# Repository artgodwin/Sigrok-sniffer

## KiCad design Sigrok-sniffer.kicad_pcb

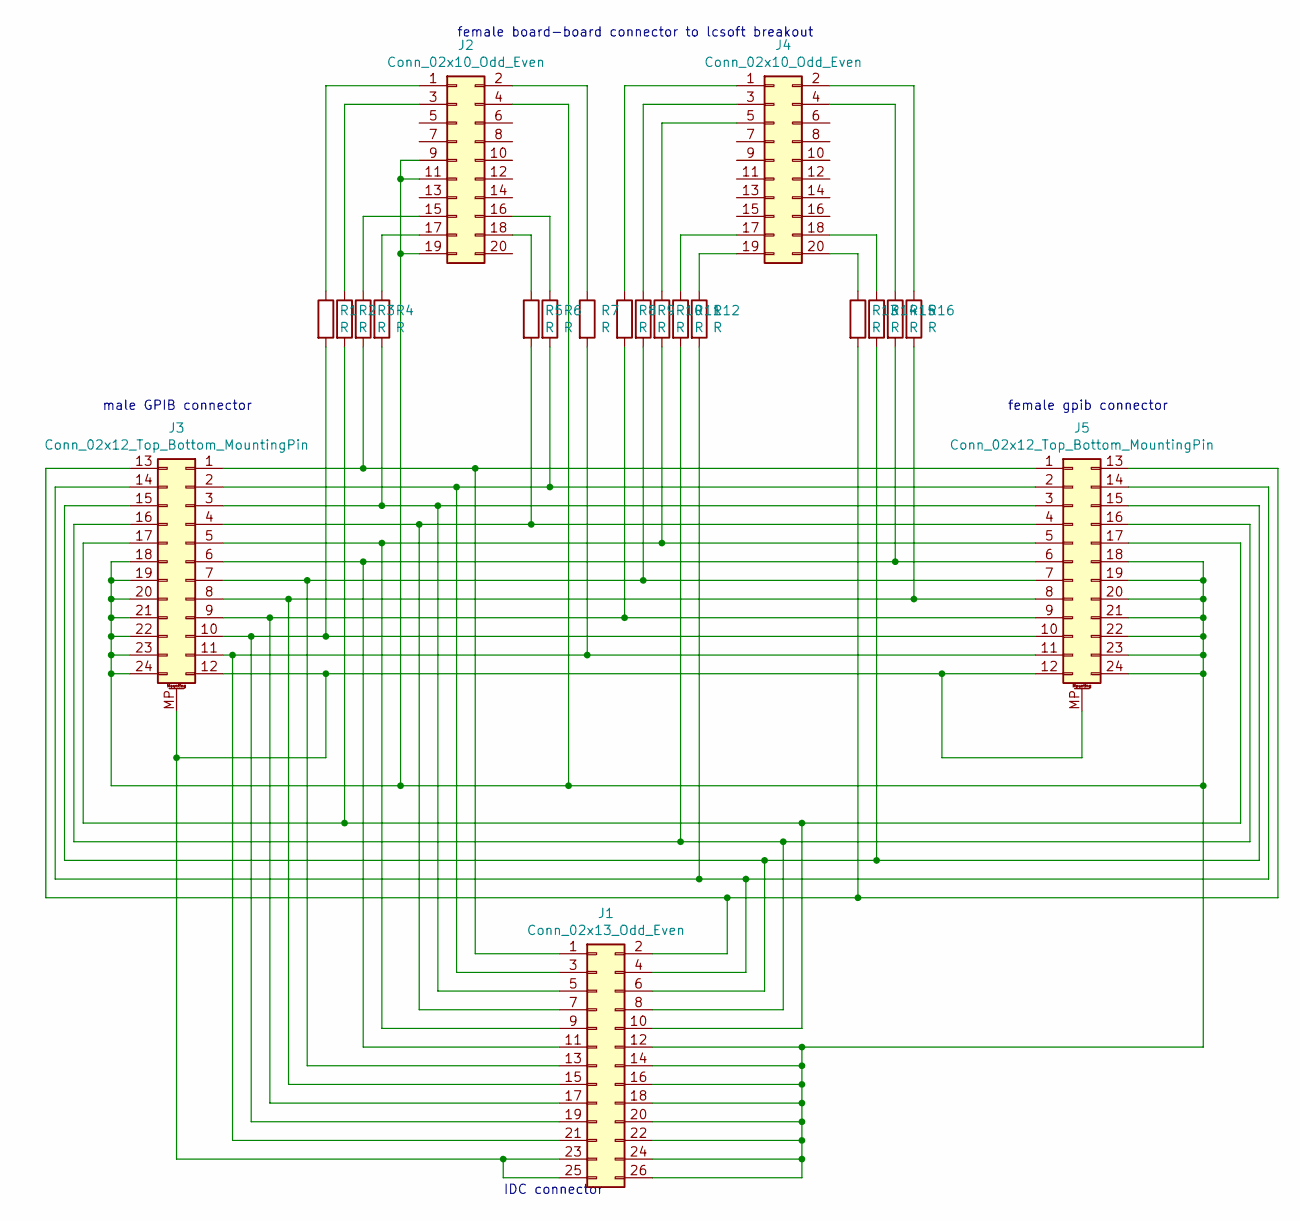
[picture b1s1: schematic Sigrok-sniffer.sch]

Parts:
J1: Conn_02x13_Odd_Even; IDC-Header_2x13_P2.54mm_Vertical
J2, J4: Conn_02x10_Odd_Even; PinHeader_2x10_P2.54mm_Vertical
J3: Conn_02x12_Top_Bottom_MountingPin; Microribbon-24_RA_Male_GPIB
J5: Conn_02x12_Top_Bottom_MountingPin; Microribbon-24_RA_Female_GPIB
R1, R2, R3, R4, R5, R6, R7, R8, R9, R10, R11, R12, R13, R14, R15, R16: R; R_0805_2012Metric

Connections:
unnamed: J1.1, J3.1, J5.1, R3.2
unnamed: J1.2, J3.13, J5.13, R13.2
unnamed: J1.3, J3.2, J5.2, R6.2
unnamed: J1.4, J3.14, J5.14, R12.2
unnamed: J1.5, J3.3, J5.3, R4.2
unnamed: J1.6, J3.15, J5.15, R14.2
unnamed: J1.7, J3.4, J5.4, R5.2
unnamed: J1.8, J3.16, J5.16, R11.2
unnamed: J1.9, J3.5, J5.5, R10.2
unnamed: J1.10, J3.17, J5.17, R2.2
unnamed: J1.11, J3.6, J5.6, R15.2
unnamed: J1.12, J1.14, J1.16, J1.18, J1.20, J1.22, J1.24, J1.26, J2.4, J2.9, J2.11, J2.19, J3.18, J3.19, J3.20, J3.21, J3.22, J3.23, J3.24, J5.18, J5.19, J5.20, J5.21, J5.22, J5.23, J5.24
unnamed: J1.13, J3.7, J5.7, R9.2
unnamed: J1.15, J3.8, J5.8, R16.2
unnamed: J1.17, J3.9, J5.9, R8.2
unnamed: J1.19, J3.10, J5.10, R1.2
unnamed: J1.21, J3.11, J5.11, R7.2
unnamed: J1.23, J1.25, J3.12, J3.MP (MountPin), J5.12, J5.MP (MountPin)
unnamed: J2.1, R1.1
unnamed: J2.2, R7.1
unnamed: J2.3, R2.1
unnamed: J2.15, R3.1
unnamed: J2.16, R6.1
unnamed: J2.17, R4.1
unnamed: J2.18, R5.1
unnamed: J4.1, R8.1
unnamed: J4.2, R16.1
unnamed: J4.3, R9.1
unnamed: J4.4, R15.1
unnamed: J4.5, R10.1
unnamed: J4.17, R11.1
unnamed: J4.18, R14.1
unnamed: J4.19, R12.1
unnamed: J4.20, R13.1

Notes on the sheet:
IDC connector
female board-board connector to lcsoft breakout
female gpib connector
male GPIB connector

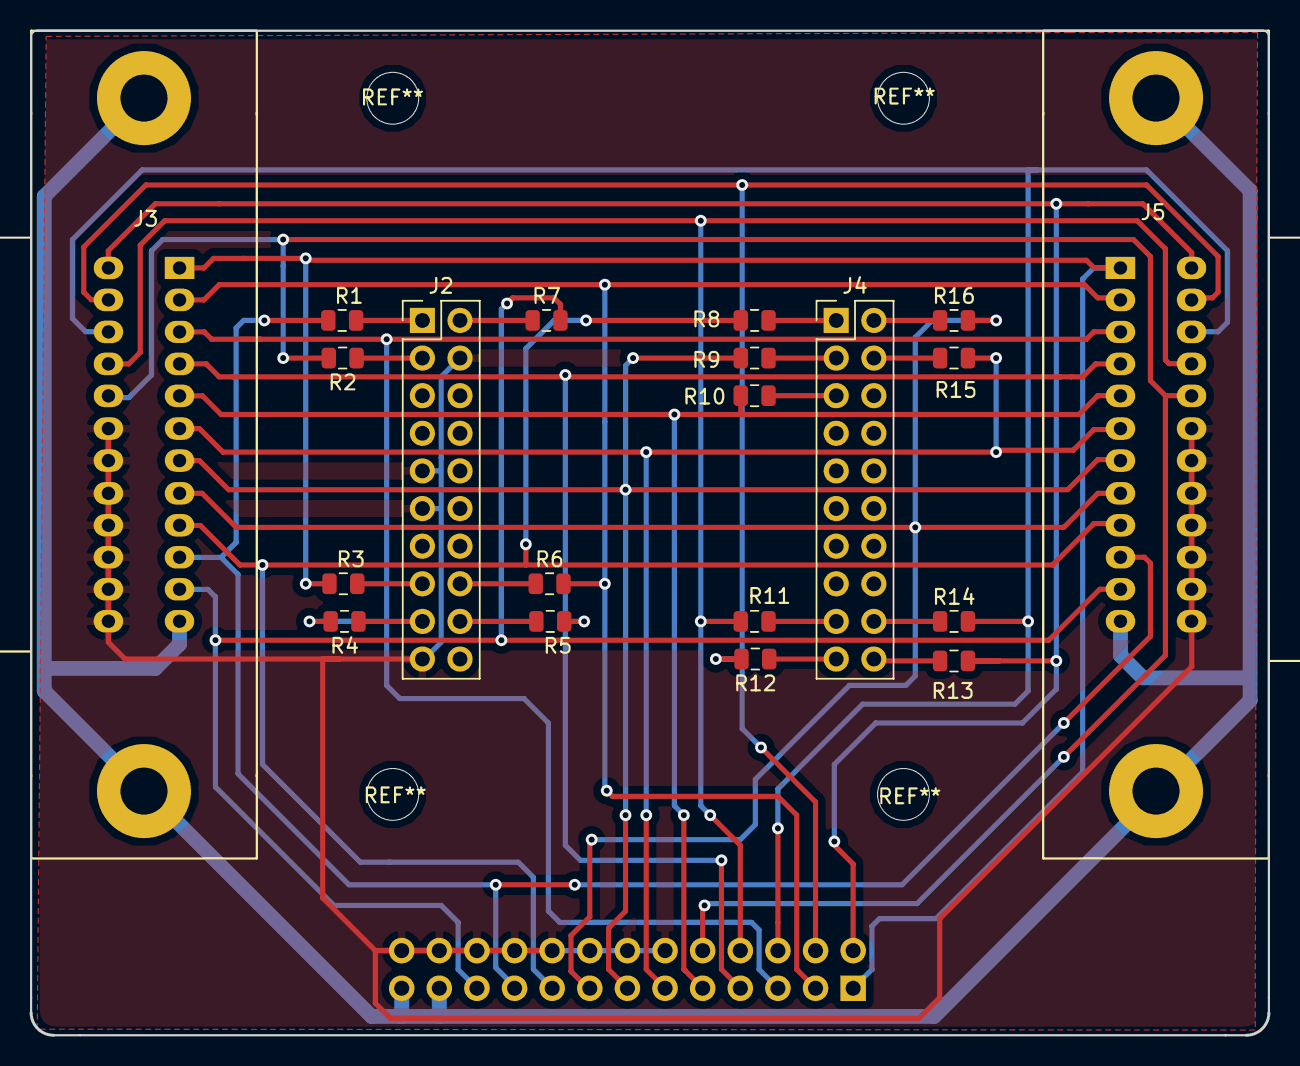
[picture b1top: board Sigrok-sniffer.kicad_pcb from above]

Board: 2 copper layers, 83.6 x 67.8 mm, 21 parts (1 on the bottom side), 34 nets.

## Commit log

2022-10-03 Added pdf schematic
2022-10-03 remove unwanted backup
